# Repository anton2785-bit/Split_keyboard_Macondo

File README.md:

# Split_keyboard_Macondo
---
## What is this project
* This is a split keyboard. That means that it has 2 separarate parts that are conected to the PC via bluethooth. This allows them to have separate layouts and to have the opportunity to be in different places whiie typing.
---
## Why i made this project
* I wanted to have a small portable keyboard that I can still use for typing and to be compact.
---
## Images 

--- 
* This is an image of the schematic:

* This is the PCB:

* The 3D model of the PCB:

* This is an image of the PCB with the frame: 

---
## Assembly
* First everything has to be souldered.
* Then You can place the keys and keycaps in the hotswap sockets.
* After that the code has to be uploaded to the XIAO.
* Then after the coding you can place the assembly into the case and be good to go.
---
## BOM
| Name | Purpose | Quantity | Total Cost (USD) | Distributor |
|------|---------|----------|-----------------|-------------|
| [nRF52840](https://www.seeedstudio.com/Seeed-XIAO-BLE-nRF52840-p-5201.html) | Connects to the PC and gets the signals from the switches | 2 | $33.50 | Seeedstudio |
| PCB | A place for all of the components | 1 | $35.00 | JLCPCB |
| [Keycaps](https://www.aliexpress.com/item/1005010777462878.html) | Make it easier to type | 4 | $22.00 | AliExpress |
| [Diodes](https://www.aliexpress.com/item/1005007160563285.html) | Stops the current in one direction | 1 | $2.10 | AliExpress |
| [Switches](https://www.gateron.com/products/gateron-ks-33-low-profile-red-silent-20-mechanical-switches-set?VariantsId=11584) | A switch | 2 | $21.28 | Gateron |
| [Hotswap modules](https://www.gateron.com/products/gateron-low-profile-switch-hot-swap-pcb-socket?VariantsId=10234) | Makes the keys easier to remove | 1 | $8.80 | Gateron |

**Total Estimated Cost: ~$123**

---
## Side note 
* I will change the code for the keyboard to a not AI  generated one. I generated it because I dont have the chips now to make it properly or test it. 
## Credits

* Designed and built by *(Anton/ Anton-2785-bit)
* Inspired by open‑source mechanical keyboard and hackpad communities (https://macondo.hackclub.com/).

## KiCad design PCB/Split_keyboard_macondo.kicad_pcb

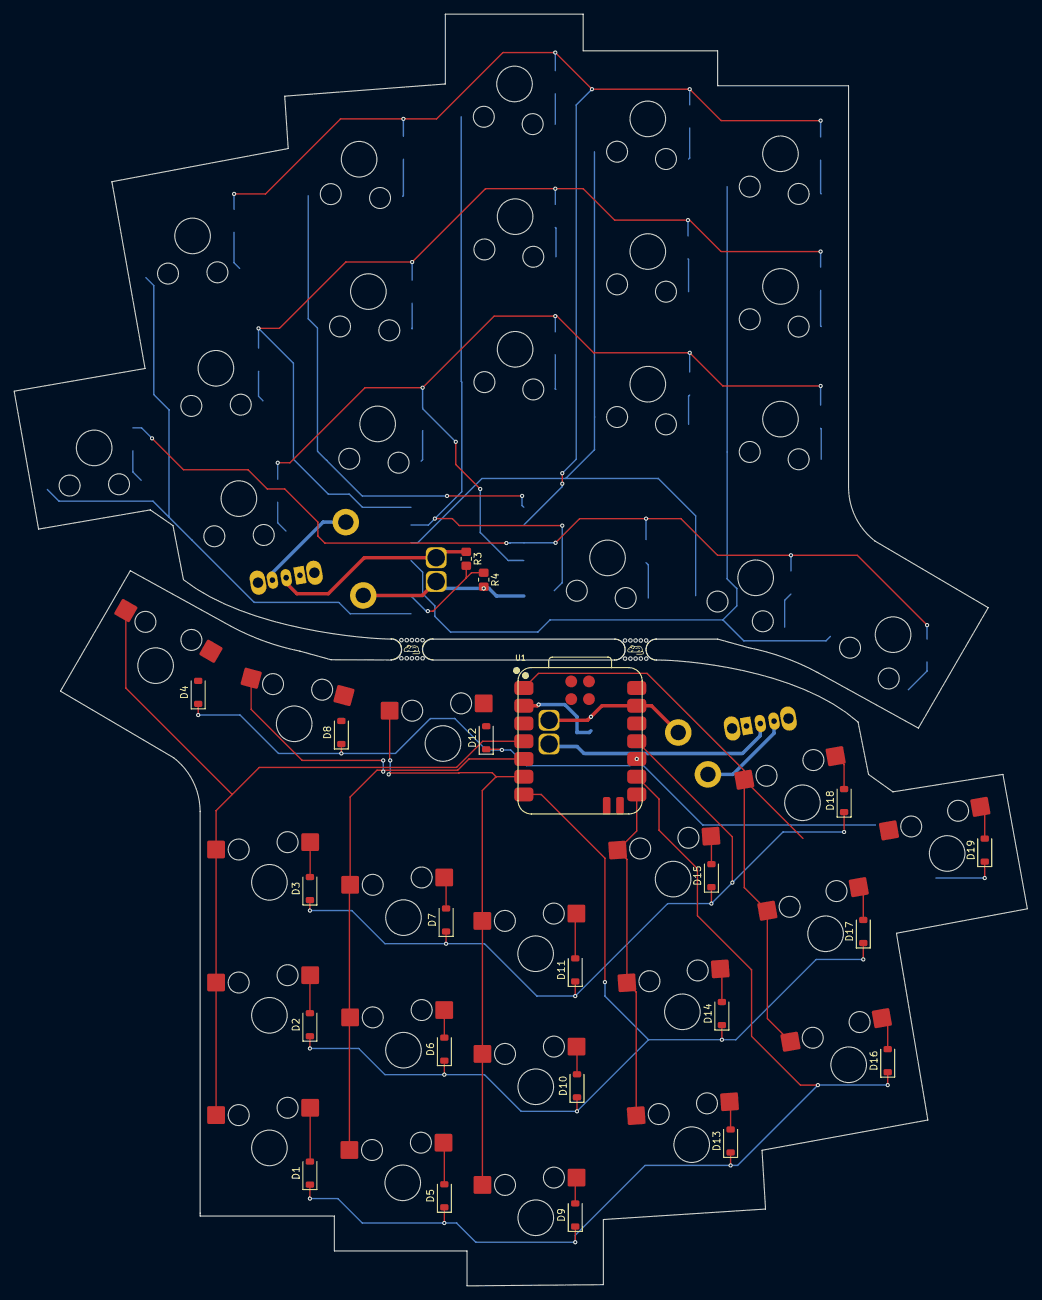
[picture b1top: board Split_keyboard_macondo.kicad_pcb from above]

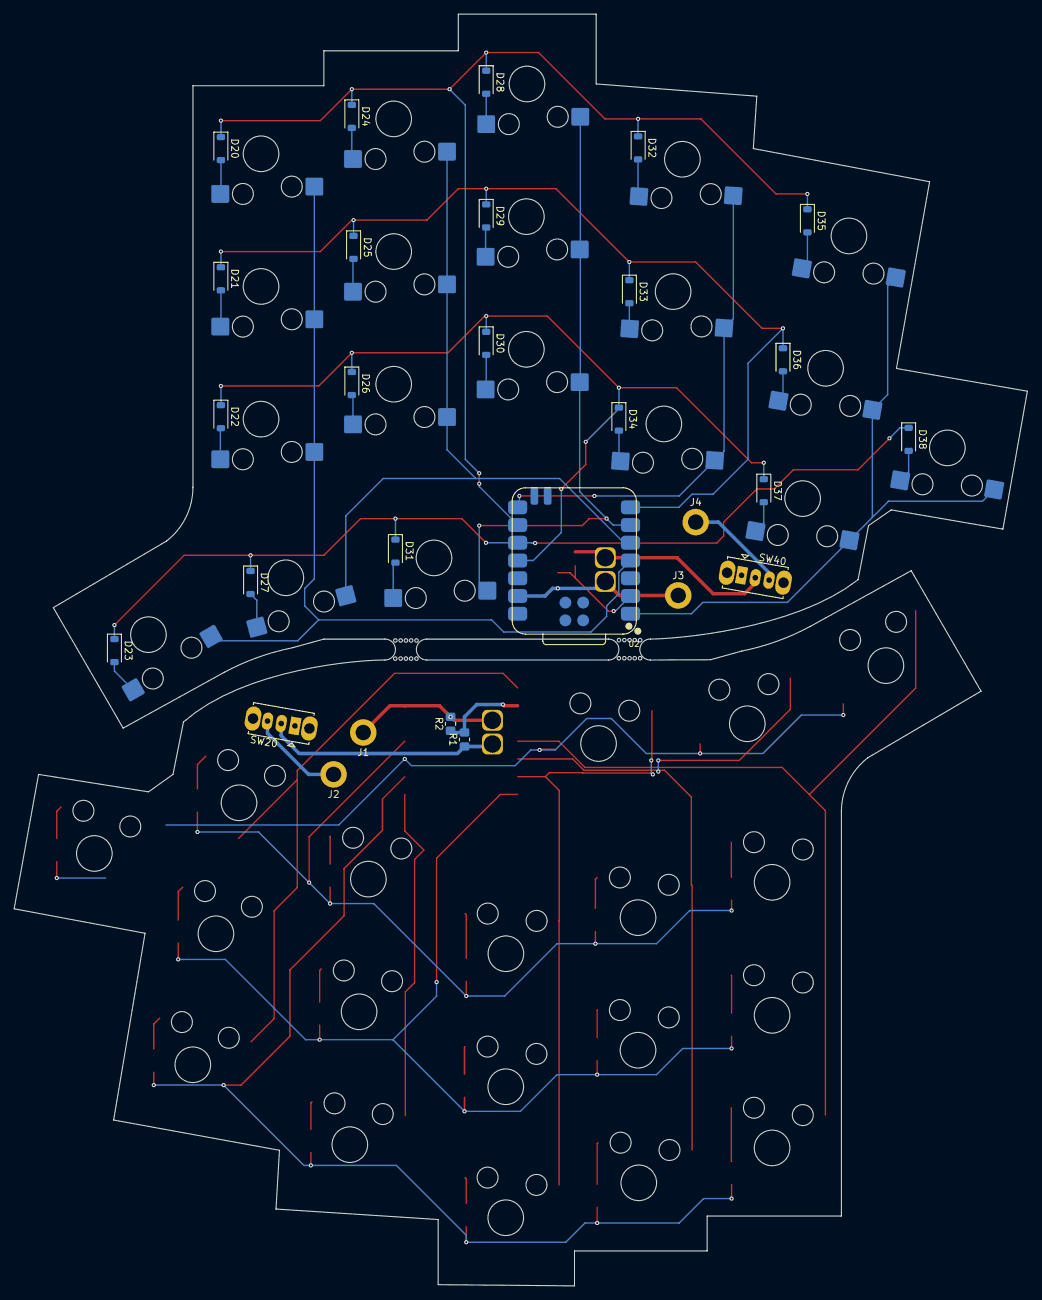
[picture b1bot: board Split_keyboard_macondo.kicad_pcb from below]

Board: 2 copper layers, 145.1 x 182.1 mm, 90 parts (47 on the bottom side), 52 nets.

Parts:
B1, B2: MouseBite; mouse-bite-3mm-6mm
D1, D2, D3, D4, D5, D6, D7, D8, D9, D10, D11, D12, D13, D14, D15, D16, D17, D18, D19, D20, D21, D22, D23, D24, D25, D26, D27, D28, D29, D30, D31, D32, D33, D34, D35, D36, D37, D38: 1N4148W; D_SOD-123
J1, J2, J3, J4: Conn_01x01_Pin; MountingHole_2.2mm_M2_DIN965_Pad
R1, R3: 806k; R_0805_2012Metric_Pad1.20x1.40mm_HandSolder
R2, R4: 2M; R_0805_2012Metric_Pad1.20x1.40mm_HandSolder
SW1, SW2, SW3, SW4, SW5, SW6, SW7, SW8, SW9, SW10, SW11, SW12, SW13, SW14, SW15, SW16, SW17, SW18, SW19, SW21, SW22, SW23, SW24, SW25, SW26, SW27, SW28, SW29, SW30, SW31, SW32, SW33, SW34, SW35, SW36, SW37, SW38, SW39: SW_Push_45deg; Gateron-KS33-Hotswap-1U
SW20, SW40: SW_Push_SPDT; SW_Slide_SPDT_Straight_CK_OS102011MS2Q
U1, U2: XIAO-nRF52840-SMD; modified-XIAO-nRF52840-SMD

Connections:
Bat +: R1.1, R3.1, SW20.2 (B), SW40.2 (B), U1.15 (BAT), U2.15 (BAT)
Bat pin +: R1.2, R2.1, R3.2, R4.1, U1.2 (P0.03_A1_D1), U2.2 (P0.03_A1_D1)
C1: SW1.1, SW2.1, SW3.1, SW4.1, SW21.1, SW22.1, SW23.1, SW24.1, U1.4 (P0.29_A3_D3), U2.4 (P0.29_A3_D3)
C2: SW5.1, SW6.1, SW7.1, SW8.1, SW25.1, SW26.1, SW27.1, SW28.1, U1.5 (P0.04_A4_D4_SDA), U2.5 (P0.04_A4_D4_SDA)
C3: SW9.1, SW10.1, SW11.1, SW12.1, SW29.1, SW30.1, SW31.1, SW32.1, U1.6 (P0.05_A5_D5_SCL), U2.6 (P0.05_A5_D5_SCL)
C4: SW13.1, SW14.1, SW15.1, SW33.1, SW34.1, SW35.1, U1.8 (P1.12_D7_RX), U2.8 (P1.12_D7_RX)
C5: SW16.1, SW17.1, SW18.1, SW19.1, SW36.1, SW37.1, SW38.1, SW39.1, U1.1 (P0.02_A0_D0), U2.1 (P0.02_A0_D0)
GND: J1.1 (Pin_1_1), J3.1 (Pin_1_1), R2.2, R4.2, U1.13 (GND), U1.16 (GND), U2.13 (GND), U2.16 (GND)
unnamed: D1.2 (A), SW1.2
unnamed: D2.2 (A), SW2.2
unnamed: D3.2 (A), SW3.2
unnamed: D4.2 (A), SW4.2
unnamed: D5.2 (A), SW5.2
unnamed: D6.2 (A), SW6.2
unnamed: D7.2 (A), SW7.2
unnamed: D8.2 (A), SW8.2
unnamed: D9.2 (A), SW9.2
unnamed: D10.2 (A), SW10.2
unnamed: D11.2 (A), SW11.2
unnamed: D12.2 (A), SW12.2
unnamed: D13.2 (A), SW13.2
unnamed: D14.2 (A), SW14.2
unnamed: D15.2 (A), SW15.2
unnamed: D16.2 (A), SW16.2
unnamed: D17.2 (A), SW17.2
unnamed: D18.2 (A), SW18.2
unnamed: D19.2 (A), SW19.2
unnamed: D20.2 (A), SW21.2
unnamed: D21.2 (A), SW22.2
unnamed: D22.2 (A), SW23.2
unnamed: D23.2 (A), SW24.2
unnamed: D24.2 (A), SW25.2
unnamed: D25.2 (A), SW26.2
unnamed: D26.2 (A), SW27.2
unnamed: D27.2 (A), SW28.2
unnamed: D28.2 (A), SW29.2
unnamed: D29.2 (A), SW30.2
unnamed: D30.2 (A), SW31.2
unnamed: D31.2 (A), SW32.2
unnamed: D32.2 (A), SW33.2
unnamed: D33.2 (A), SW34.2
unnamed: D34.2 (A), SW35.2
unnamed: D35.2 (A), SW36.2
unnamed: D36.2 (A), SW37.2
unnamed: D37.2 (A), SW38.2
unnamed: D38.2 (A), SW39.2
unnamed: J2.1 (Pin_1_1), SW20.3 (C)
unnamed: J4.1 (Pin_1_1), SW40.3 (C)
R1: D1.1 (K), D5.1 (K), D9.1 (K), D13.1 (K), D16.1 (K), D20.1 (K), D24.1 (K), D28.1 (K), D32.1 (K), D35.1 (K), U1.9 (P1.13_D8_SCK), U2.9 (P1.13_D8_SCK)
R2: D2.1 (K), D6.1 (K), D10.1 (K), D14.1 (K), D17.1 (K), D21.1 (K), D25.1 (K), D29.1 (K), D33.1 (K), D36.1 (K), U1.7 (P1.11_D6_TX), U2.7 (P1.11_D6_TX)
R3: D3.1 (K), D7.1 (K), D11.1 (K), D15.1 (K), D18.1 (K), D22.1 (K), D26.1 (K), D30.1 (K), D34.1 (K), D37.1 (K), U1.11 (P1.15_D10_MOSI), U2.11 (P1.15_D10_MOSI)
R4: D4.1 (K), D8.1 (K), D12.1 (K), D19.1 (K), D23.1 (K), D27.1 (K), D31.1 (K), D38.1 (K), U1.10 (P1.14_D9_MISO), U2.10 (P1.14_D9_MISO)

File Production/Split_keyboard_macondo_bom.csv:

Designator,Footprint,Quantity,Value,LCSC Part #
"D1, D10, D11, D12, D13, D14, D15, D16, D17, D18, D19, D2, D20, D21, D22, D23, D24, D25, D26, D27, D28, D29, D3, D30, D31, D32, D33, D34, D35, D36, D37, D38, D4, D5, D6, D7, D8, D9",D_SOD-123,38,1N4148W,
"J1, J2, J3, J4",MountingHole_2.2mm_M2_DIN965_Pad,4,Conn_01x01_Pin,
"R1, R3",0805,2,806k,
"R2, R4",0805,2,2M,
"SW1, SW10, SW11, SW12, SW13, SW14, SW15, SW16, SW17, SW18, SW19, SW2, SW21, SW22, SW23, SW24, SW25, SW26, SW27, SW28, SW29, SW3, SW30, SW31, SW32, SW33, SW34, SW35, SW36, SW37, SW38, SW39, SW4, SW5, SW6, SW7, SW8, SW9",Gateron-KS33-Hotswap-1U,38,SW_Push_45deg,
"SW20, SW40",SW_Slide_SPDT_Straight_CK_OS102011MS2Q,2,SW_Push_SPDT,
"U1, U2",modified-XIAO-nRF52840-SMD,2,XIAO-nRF52840-SMD,

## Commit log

2026-06-19 File update
